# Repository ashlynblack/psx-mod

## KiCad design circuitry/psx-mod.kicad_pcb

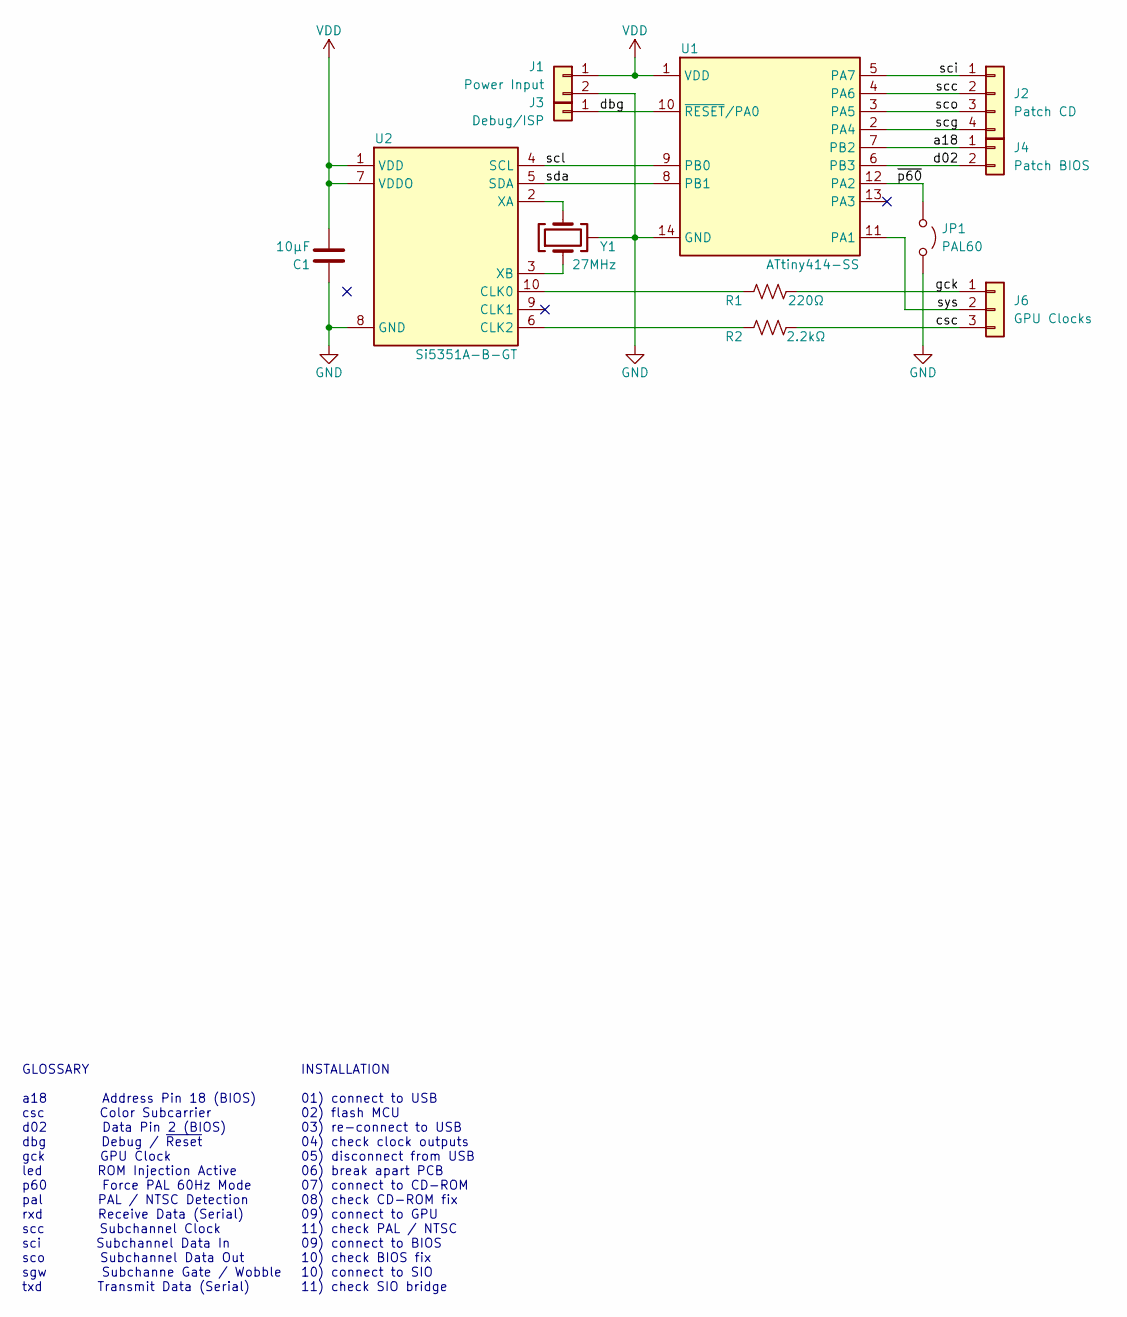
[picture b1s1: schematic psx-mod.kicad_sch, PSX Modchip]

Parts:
C1: 10µF; C_0603_1608Metric_Pad1.08x0.95mm_HandSolder
J1, J4: Conn_01x02; CONN-SMD_2P
J2: Conn_01x04; CONN-SMD_4P
J3: Conn_01x01; CONN-SMD_1P
J6: Conn_01x03; CONN-SMD_3P
JP1: Jumper_2_Open; SolderJumper-2_P1.3mm_Open_RoundedPad1.0x1.5mm
R1: 220Ω; R_0603_1608Metric_Pad0.98x0.95mm_HandSolder
R2: 2.2kΩ; R_0603_1608Metric_Pad0.98x0.95mm_HandSolder
U1: ATtiny414-SS; SOIC-14_3.9x8.7mm_P1.27mm
U2: Si5351A-B-GT; MSOP-10_3x3mm_P0.5mm
Y1: 27MHz; Crystal_SMD_3225-4Pin_3.2x2.5mm

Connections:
/a18: J4.1, U1.7 (PB2)
/csc: J6.3, R2.2
/d02: J4.2, U1.6 (PB3)
/dbg: J3.1, U1.10 (~RESET/PA0)
/gck: J6.1, R1.2
/scc: J2.2, U1.4 (PA6)
/scg: J2.4, U1.2 (PA4)
/sci: J2.1, U1.5 (PA7)
/scl: U1.9 (PB0), U2.4 (SCL)
/sco: J2.3, U1.3 (PA5)
/sda: U1.8 (PB1), U2.5 (SDA)
/sys: J6.2, U1.11 (PA1)
/~p60: JP1.1 (A), U1.12 (PA2)
GND: C1.2, J1.2, JP1.2 (B), U1.14 (GND), U2.8 (GND), Y1.2 (GND), Y1.4 (GND)
unnamed: R1.1, U2.10 (CLK0)
unnamed: R2.1, U2.6 (CLK2)
unnamed: U2.2 (XA), Y1.3
unnamed: U2.3 (XB), Y1.1
VDD: C1.1, J1.1, U1.1 (VDD), U2.1 (VDD), U2.7 (VDDO)

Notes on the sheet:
GLOSSARY a18 Address Pin 18 (BIOS) csc Color Subcarrier d02 Data Pin 2 (BIOS) dbg Debug / ~{Reset} gck GPU Clock led ROM Injection Active p60 Force PAL 60Hz Mode pal PAL / NTSC Detection rxd Receive Data (Serial) scc Subchannel Clock sci Subchannel Data In sco Subchannel Data Out sgw Subchanne Gate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
INSTALLATION 01) connect to USB 02) flash MCU 03) re-connect to USB 04) check clock outputs 05) disconnect from USB 06) break apart PCB 07) connect to CD-ROM 08) check CD-ROM fix 09) connect to GPU 11) check PAL / NTSC 09) connect to BIOS 10) check BIOS fix 10) connect to SIO 11) check SIO bridge

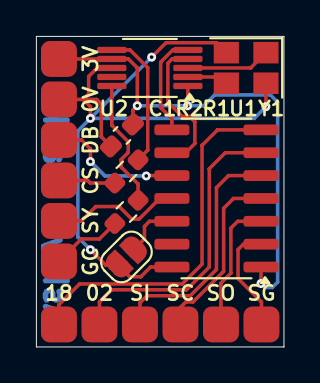
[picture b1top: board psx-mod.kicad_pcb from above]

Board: 2 copper layers, 13.8 x 17.2 mm, 12 parts (0 on the bottom side), 19 nets.

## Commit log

2024-06-03 Ignored KiCAD backups.
2024-06-03 Initial schematic.
2024-07-09 Tracked PDF, JPG, PNG and ZIP files with Git LFS.
2024-07-09 Added datasheets, articles and anterior projects to research.
2024-07-09 Completed schematic and layout (badly).
2024-07-09 Rendered model, generated gerbers, schematic and layout.
2024-07-09 Added handwritten notes to research.
2024-07-10 Generated interactive bill of materials.
2024-07-27 Ignore KiCAD backup files.
2024-07-27 Added articles on I2C to research.
2024-07-27 Completed schematic and layout.
2024-07-27 Generated artifacts.
